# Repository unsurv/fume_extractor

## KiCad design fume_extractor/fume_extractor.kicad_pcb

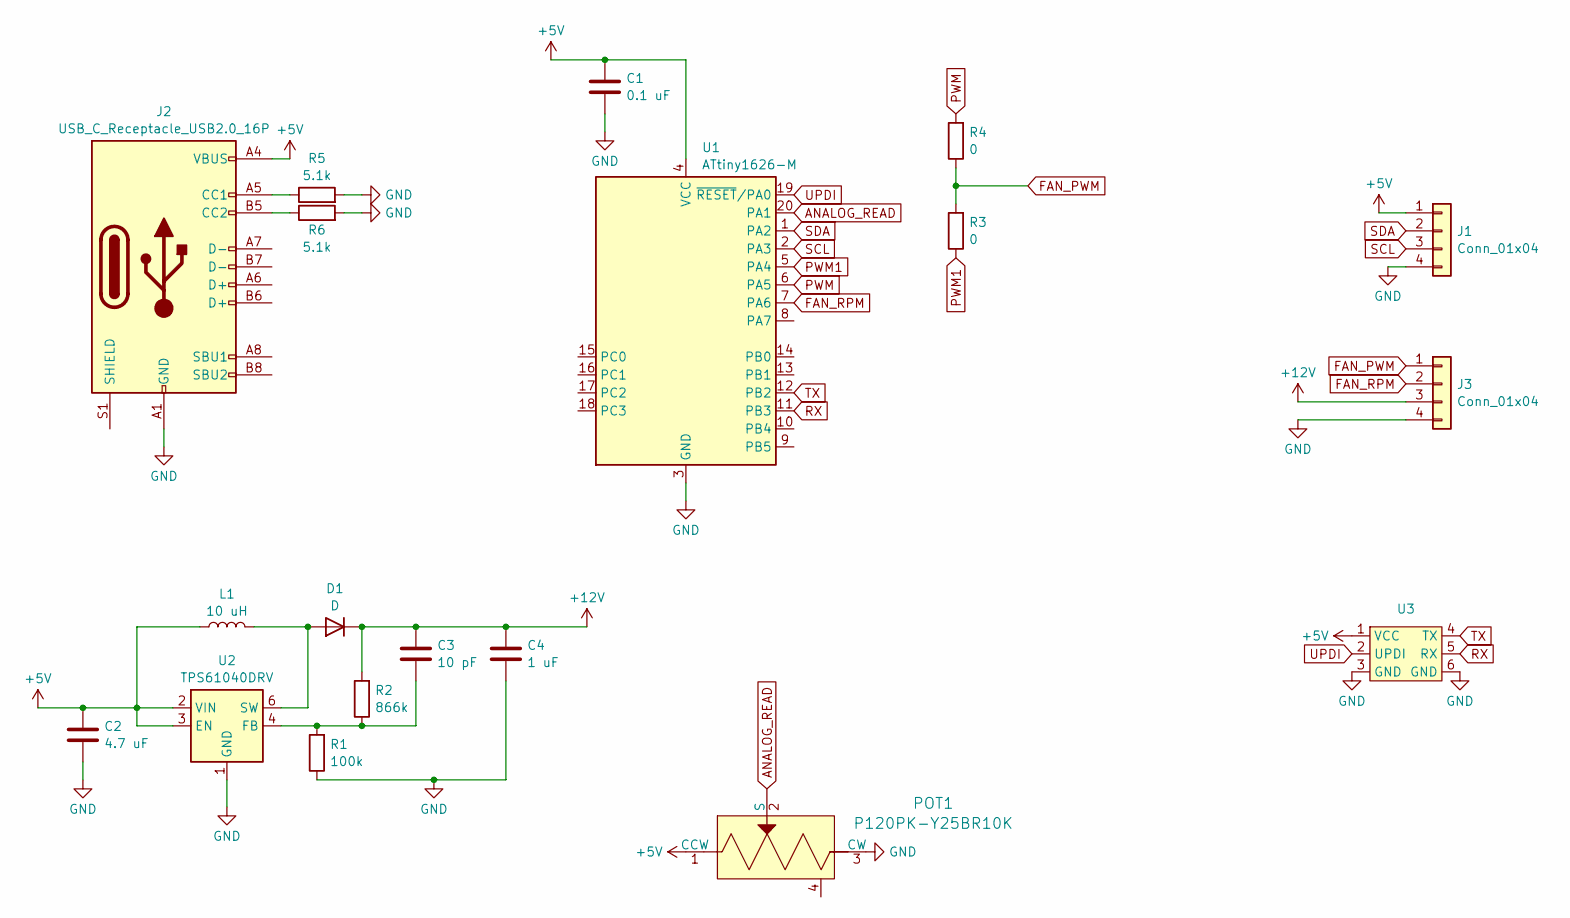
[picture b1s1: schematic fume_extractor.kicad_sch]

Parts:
C1: 0.1 uF; C_0603_1608Metric
C2: 4.7 uF; C_0603_1608Metric
C3: 10 pF; C_0603_1608Metric
C4: 1 uF; C_0603_1608Metric
D1: D; D_SOD-123
J1, J3: Conn_01x04; PinHeader_1x04_P2.54mm_Vertical
J2: USB_C_Receptacle_USB2.0_16P; USB_C_Receptacle_GCT_USB4110
L1: 10 uH; CR32
POT1: P120PK-Y25BR10K; Potentiometer_P120PK-Y25BR10K; MPN P120PK-Y25BR10K; Digi-Key_PN 987-1710-ND
R1: 100k; R_0603_1608Metric
R2: 866k; R_0603_1608Metric
R3, R4: 0; R_0603_1608Metric
R5, R6: 5.1k; R_0603_1608Metric
U1: ATtiny1626-M; VQFN-20-1EP_3x3mm_P0.4mm_EP1.7x1.7mm
U2: TPS61040DRV; WSON-6-1EP_2x2mm_P0.65mm_EP1x1.6mm
U3: testpoint_array_2x3

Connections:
+5V: C1.1, C2.1, J1.1, J2.A4 (VBUS), J2.A9 (VBUS), J2.B4 (VBUS), J2.B9 (VBUS), L1.1, POT1.1 (CCW), U1.4 (VCC), U2.2 (VIN), U2.3 (EN), U3.1 (VCC)
+12V: C3.1, C4.1, D1.1 (K), J3.3, R2.2
ANALOG_READ: POT1.2 (S), U1.20 (PA1)
FAN_PWM: J3.1, R3.2, R4.1
FAN_RPM: J3.2, U1.7 (PA6)
GND: C1.2, C2.2, C4.2, J1.4, J2.A1 (GND), J2.A12 (GND), J2.B1 (GND), J2.B12 (GND), J3.4, POT1.3 (CW), R1.1, R5.2, R6.2, U1.3 (GND), U1.21 (GND), U2.1 (GND), U3.3 (GND), U3.6 (GND)
unnamed: D1.2 (A), L1.2, U2.6 (SW)
unnamed: J2.A5 (CC1), R5.1
unnamed: J2.B5 (CC2), R6.1
unnamed: C3.2, R1.2, R2.1, U2.4 (FB)
PWM: R4.2, U1.6 (PA5)
PWM1: R3.1, U1.5 (PA4)
RX: U1.11 (PB3), U3.5 (RX)
SCL: J1.3, U1.2 (PA3)
SDA: J1.2, U1.1 (PA2)
TX: U1.12 (PB2), U3.4 (TX)
UPDI: U1.19 (~RESET/PA0), U3.2 (UPDI)

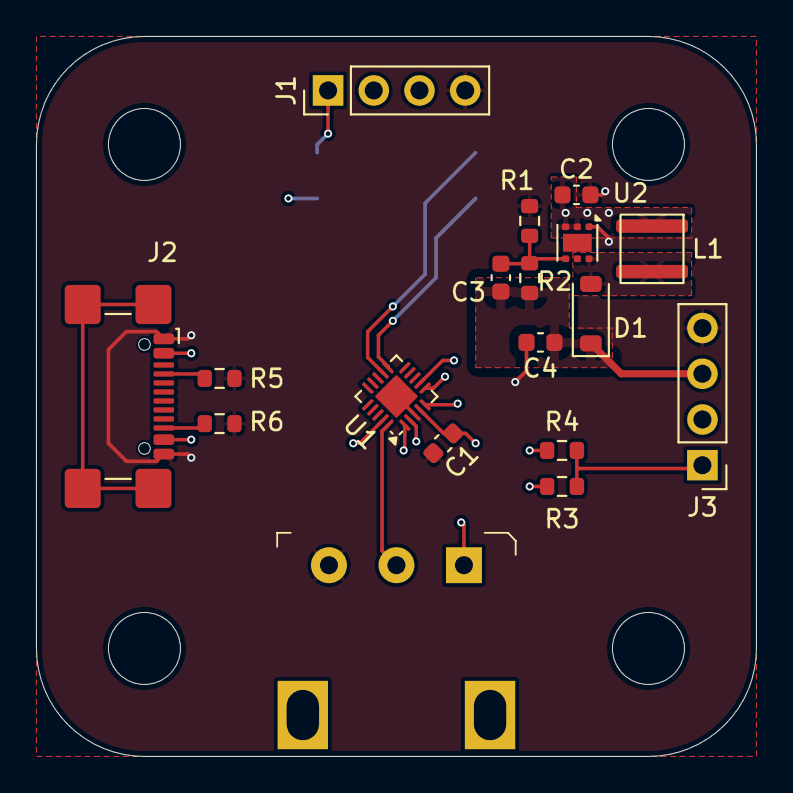
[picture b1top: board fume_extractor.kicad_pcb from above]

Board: 4 copper layers, 40.0 x 40.0 mm, 19 parts (1 on the bottom side), 17 nets.

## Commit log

2025-08-08 parts + schematic
2025-08-12 rev 1
2025-08-29 fix GND connection on USB C
